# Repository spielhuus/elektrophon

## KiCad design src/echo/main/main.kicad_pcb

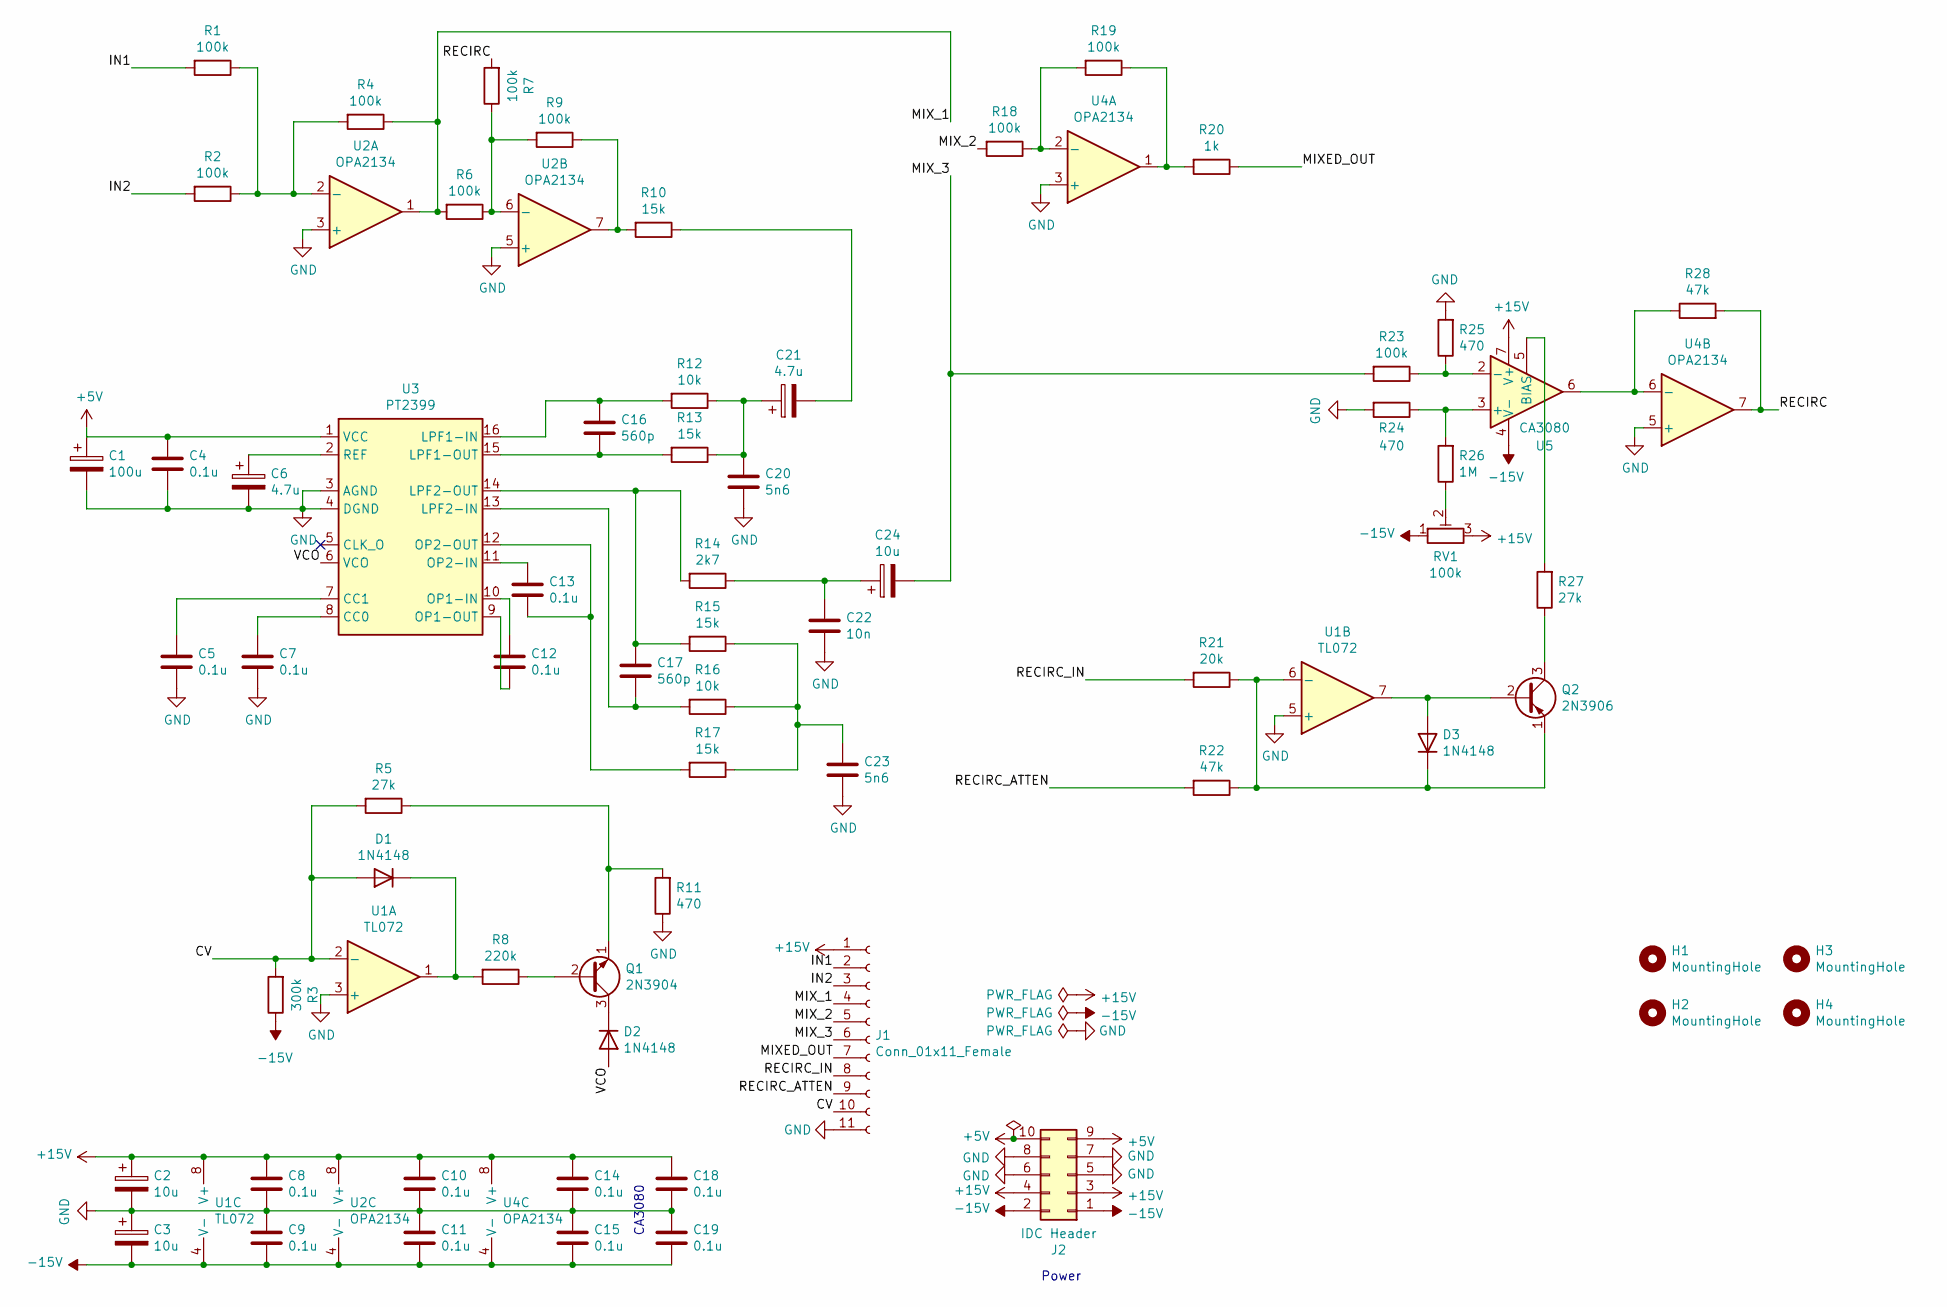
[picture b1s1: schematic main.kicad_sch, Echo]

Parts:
C1: 100u; CP_Radial_D8.0mm_P3.50mm
C2, C3, C24: 10u; CP_Radial_D5.0mm_P2.50mm
C4, C5, C7, C8, C9, C10, C11, C12, C13, C14, C15, C18, C19: 0.1u; C_Rect_L4.0mm_W2.5mm_P2.50mm
C6, C21: 4.7u; CP_Radial_D5.0mm_P2.00mm
C16, C17: 560p; C_Rect_L4.0mm_W2.5mm_P2.50mm
C20, C23: 5n6; C_Rect_L4.6mm_W3.8mm_P2.50mm_MKS02_FKP02
C22: 10n; C_Rect_L4.0mm_W2.5mm_P2.50mm
D1, D2, D3: 1N4148; D_DO-35_SOD27_P7.62mm_Horizontal
H1, H2, H3, H4: MountingHole; MountingHole_2.2mm_M2
J1: Conn_01x11_Female; PinHeader_1x11_P2.54mm_Vertical
J2: IDC Header; IDC-Header_2x05_P2.54mm_Vertical
Q1: 2N3904; TO-92_Inline_Wide
Q2: 2N3906; TO-92_Inline_Wide
R1, R2, R4, R6, R7, R9, R18, R19, R23: 100k; R_Axial_DIN0207_L6.3mm_D2.5mm_P10.16mm_Horizontal
R3: 300k; R_Axial_DIN0207_L6.3mm_D2.5mm_P10.16mm_Horizontal
R5, R27: 27k; R_Axial_DIN0207_L6.3mm_D2.5mm_P10.16mm_Horizontal
R8: 220k; R_Axial_DIN0207_L6.3mm_D2.5mm_P10.16mm_Horizontal
R10, R13, R15, R17: 15k; R_Axial_DIN0207_L6.3mm_D2.5mm_P10.16mm_Horizontal
R11, R24, R25: 470; R_Axial_DIN0207_L6.3mm_D2.5mm_P10.16mm_Horizontal
R12, R16: 10k; R_Axial_DIN0207_L6.3mm_D2.5mm_P10.16mm_Horizontal
R14: 2k7; R_Axial_DIN0207_L6.3mm_D2.5mm_P10.16mm_Horizontal
R20: 1k; R_Axial_DIN0207_L6.3mm_D2.5mm_P10.16mm_Horizontal
R21: 20k; R_Axial_DIN0207_L6.3mm_D2.5mm_P10.16mm_Horizontal
R22, R28: 47k; R_Axial_DIN0207_L6.3mm_D2.5mm_P10.16mm_Horizontal
R26: 1M; R_Axial_DIN0207_L6.3mm_D2.5mm_P10.16mm_Horizontal
RV1: 100k; Potentiometer_Bourns_3296Z_Horizontal
U1: TL072; DIP-8_W7.62mm_Socket
U2, U4: OPA2134; DIP-8_W7.62mm_Socket
U3: PT2399; DIP-16_W7.62mm_Socket
U5: CA3080; DIP-8_W7.62mm_Socket

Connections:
+5V: C1.1, C4.1, J2.9, J2.10, U3.1 (VCC)
+15V: C2.1, C8.1, C10.1, C14.1, C18.1, J1.1, J2.3, J2.4, RV1.3, U1.8 (V+), U2.8 (V+), U4.8 (V+), U5.7 (V+)
-15V: C3.2, C9.2, C11.2, C15.2, C19.2, J2.1, J2.2, R3.1, RV1.1, U1.4 (V-), U2.4 (V-), U4.4 (V-), U5.4 (V-)
/CV: D1.2 (A), J1.10, R3.2, R5.2, U1.2 (-)
/IN1: J1.2, R1.2
/IN2: J1.3, R2.2
/MIXED_OUT: J1.7, R20.1
/MIX_1: J1.4, R4.1, R6.2, U2.1
/MIX_2: J1.5, R18.2
/MIX_3: C24.2, J1.6, R23.2
/RECIRC: R7.2, R28.2, U4.7
/RECIRC_ATTEN: J1.9, R22.2
/RECIRC_IN: J1.8, R21.2
/VCO: D2.2 (A), U3.6 (VCO)
GND: C1.2, C2.2, C3.1, C4.2, C5.2, C6.2, C7.2, C8.2, C9.1, C10.2, C11.1, C14.2, C15.1, C18.2, C19.1, C20.2, C22.2, C23.2, J1.11, J2.5, J2.6, J2.7, J2.8, R11.1, R24.2, R25.2, U1.3 (+), U1.5 (+), U2.3 (+), U2.5 (+), U3.3 (AGND), U3.4 (DGND), U4.3 (+), U4.5 (+)
unnamed: C20.1, C21.1, R12.1, R13.1
unnamed: C21.2, R10.1
unnamed: C22.1, C24.1, R14.1
unnamed: C23.1, R15.1, R16.1, R17.1
unnamed: D1.1 (K), R8.2, U1.1
unnamed: D2.1 (K), Q1.3 (C)
unnamed: D3.2 (A), Q2.2 (B), U1.7
unnamed: D3.1 (K), Q2.1 (E), R21.1, R22.1, U1.6 (-)
unnamed: Q1.2 (B), R8.1
unnamed: Q1.1 (E), R5.1, R11.2
unnamed: Q2.3 (C), R27.1
unnamed: R9.1, R10.2, U2.7
unnamed: R19.1, R20.2, U4.1
unnamed: R26.1, RV1.2
unnamed: R1.1, R2.1, R4.2, U2.2 (-)
unnamed: R6.1, R7.1, R9.2, U2.6 (-)
unnamed: C7.1, U3.8 (CC0)
unnamed: C5.1, U3.7 (CC1)
unnamed: C16.1, R12.2, U3.16 (LPF1-IN)
unnamed: C16.2, R13.2, U3.15 (LPF1-OUT)
unnamed: C17.2, R16.2, U3.13 (LPF2-IN)
unnamed: C17.1, R14.2, R15.2, U3.14 (LPF2-OUT)
unnamed: C12.1, U3.10 (OP1-IN)
unnamed: C12.2, U3.9 (OP1-OUT)
unnamed: C13.1, U3.11 (OP2-IN)
unnamed: C13.2, R17.2, U3.12 (OP2-OUT)
unnamed: C6.1, U3.2 (REF)
unnamed: R18.1, R19.2, U4.2 (-)
unnamed: R28.1, U4.6 (-), U5.6
unnamed: R24.1, R26.2, U5.3 (+)
unnamed: R23.1, R25.1, U5.2 (-)
unnamed: R27.2, U5.5 (BIAS)

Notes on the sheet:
CA3080
Power

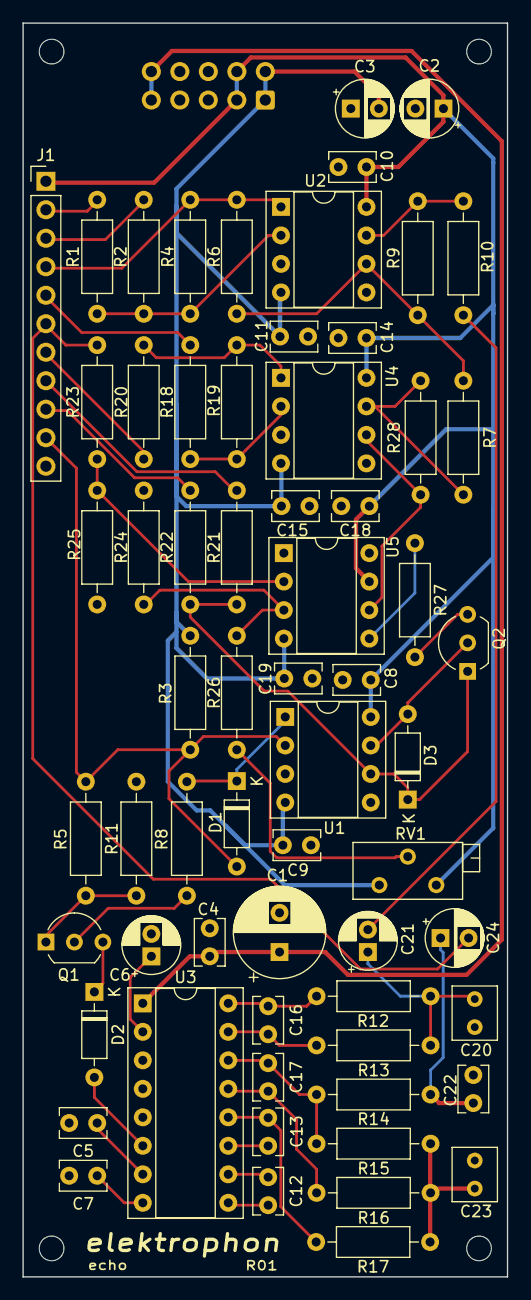
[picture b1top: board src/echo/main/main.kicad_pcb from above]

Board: 2 copper layers, 43.2 x 111.8 mm, 69 parts (1 on the bottom side), 47 nets.

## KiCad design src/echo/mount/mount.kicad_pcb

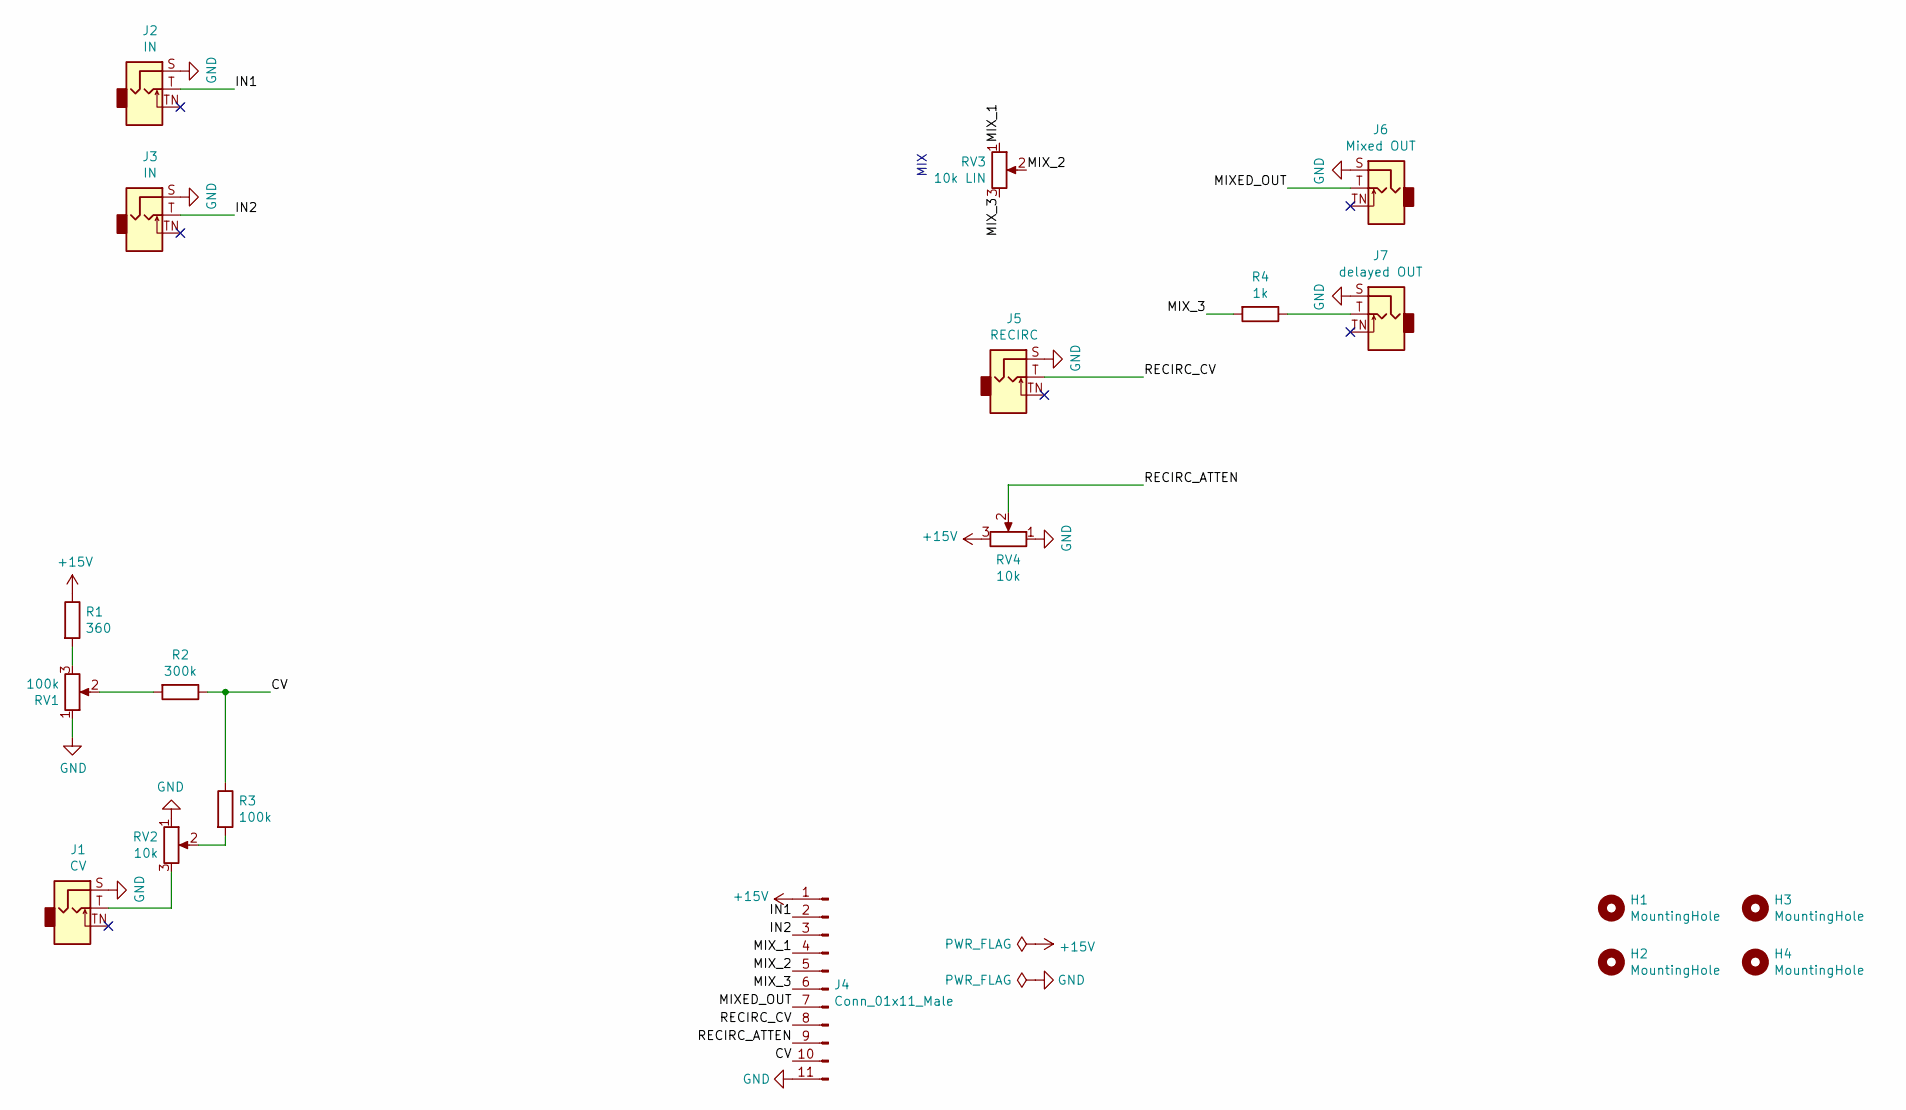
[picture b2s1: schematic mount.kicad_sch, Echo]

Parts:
H1, H2, H3, H4: MountingHole; MountingHole_2.2mm_M2
J1: CV; Jack_3.5mm_WQP-PJ398SM_Vertical
J2, J3: IN; Jack_3.5mm_WQP-PJ398SM_Vertical
J4: Conn_01x11_Male; PinHeader_1x11_P2.54mm_Vertical
J5: RECIRC; Jack_3.5mm_WQP-PJ398SM_Vertical
J6: Mixed OUT; Jack_3.5mm_WQP-PJ398SM_Vertical
J7: delayed OUT; Jack_3.5mm_WQP-PJ398SM_Vertical
R1: 360; R_Axial_DIN0207_L6.3mm_D2.5mm_P10.16mm_Horizontal
R2: 300k; R_Axial_DIN0207_L6.3mm_D2.5mm_P10.16mm_Horizontal
R3: 100k; R_Axial_DIN0207_L6.3mm_D2.5mm_P10.16mm_Horizontal
R4: 1k; R_Axial_DIN0207_L6.3mm_D2.5mm_P10.16mm_Horizontal
RV1: 100k; Potentiometer_Alpha_RD901F-40-00D_Single_Vertical
RV2, RV4: 10k; Potentiometer_Alpha_RD901F-40-00D_Single_Vertical
RV3: 10k LIN; Potentiometer_Alpha_RD901F-40-00D_Single_Vertical

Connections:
+15V: J4.1, R1.1, RV4.3
/CV: J4.10, R2.1, R3.1
/IN1: J2.T, J4.2
/IN2: J3.T, J4.3
/MIXED_OUT: J4.7, J6.T
/MIX_1: J4.4, RV3.1
/MIX_2: J4.5, RV3.2
/MIX_3: J4.6, R4.2, RV3.3
/RECIRC_ATTEN: J4.9, RV4.2
/RECIRC_CV: J4.8, J5.T
GND: J1.S, J2.S, J3.S, J4.11, J5.S, J6.S, J7.S, RV1.1, RV2.1, RV4.1
unnamed: J1.T, RV2.3
unnamed: J7.T, R4.1
unnamed: R1.2, RV1.3
unnamed: R2.2, RV1.2
unnamed: R3.2, RV2.2

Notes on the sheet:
MIX

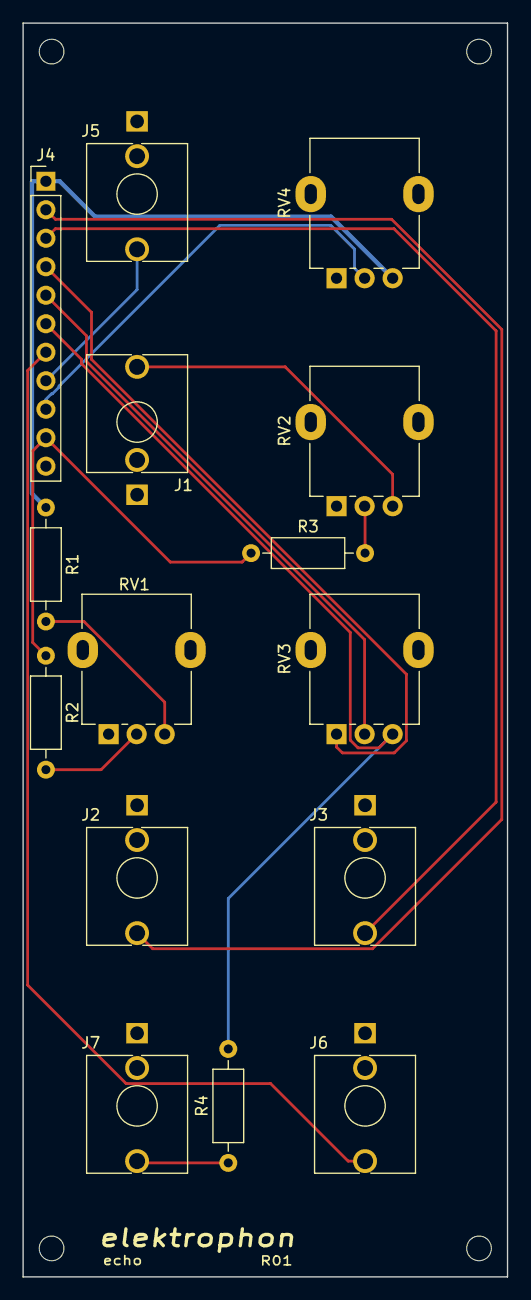
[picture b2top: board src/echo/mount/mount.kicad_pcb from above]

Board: 2 copper layers, 43.2 x 111.8 mm, 19 parts (0 on the bottom side), 16 nets.

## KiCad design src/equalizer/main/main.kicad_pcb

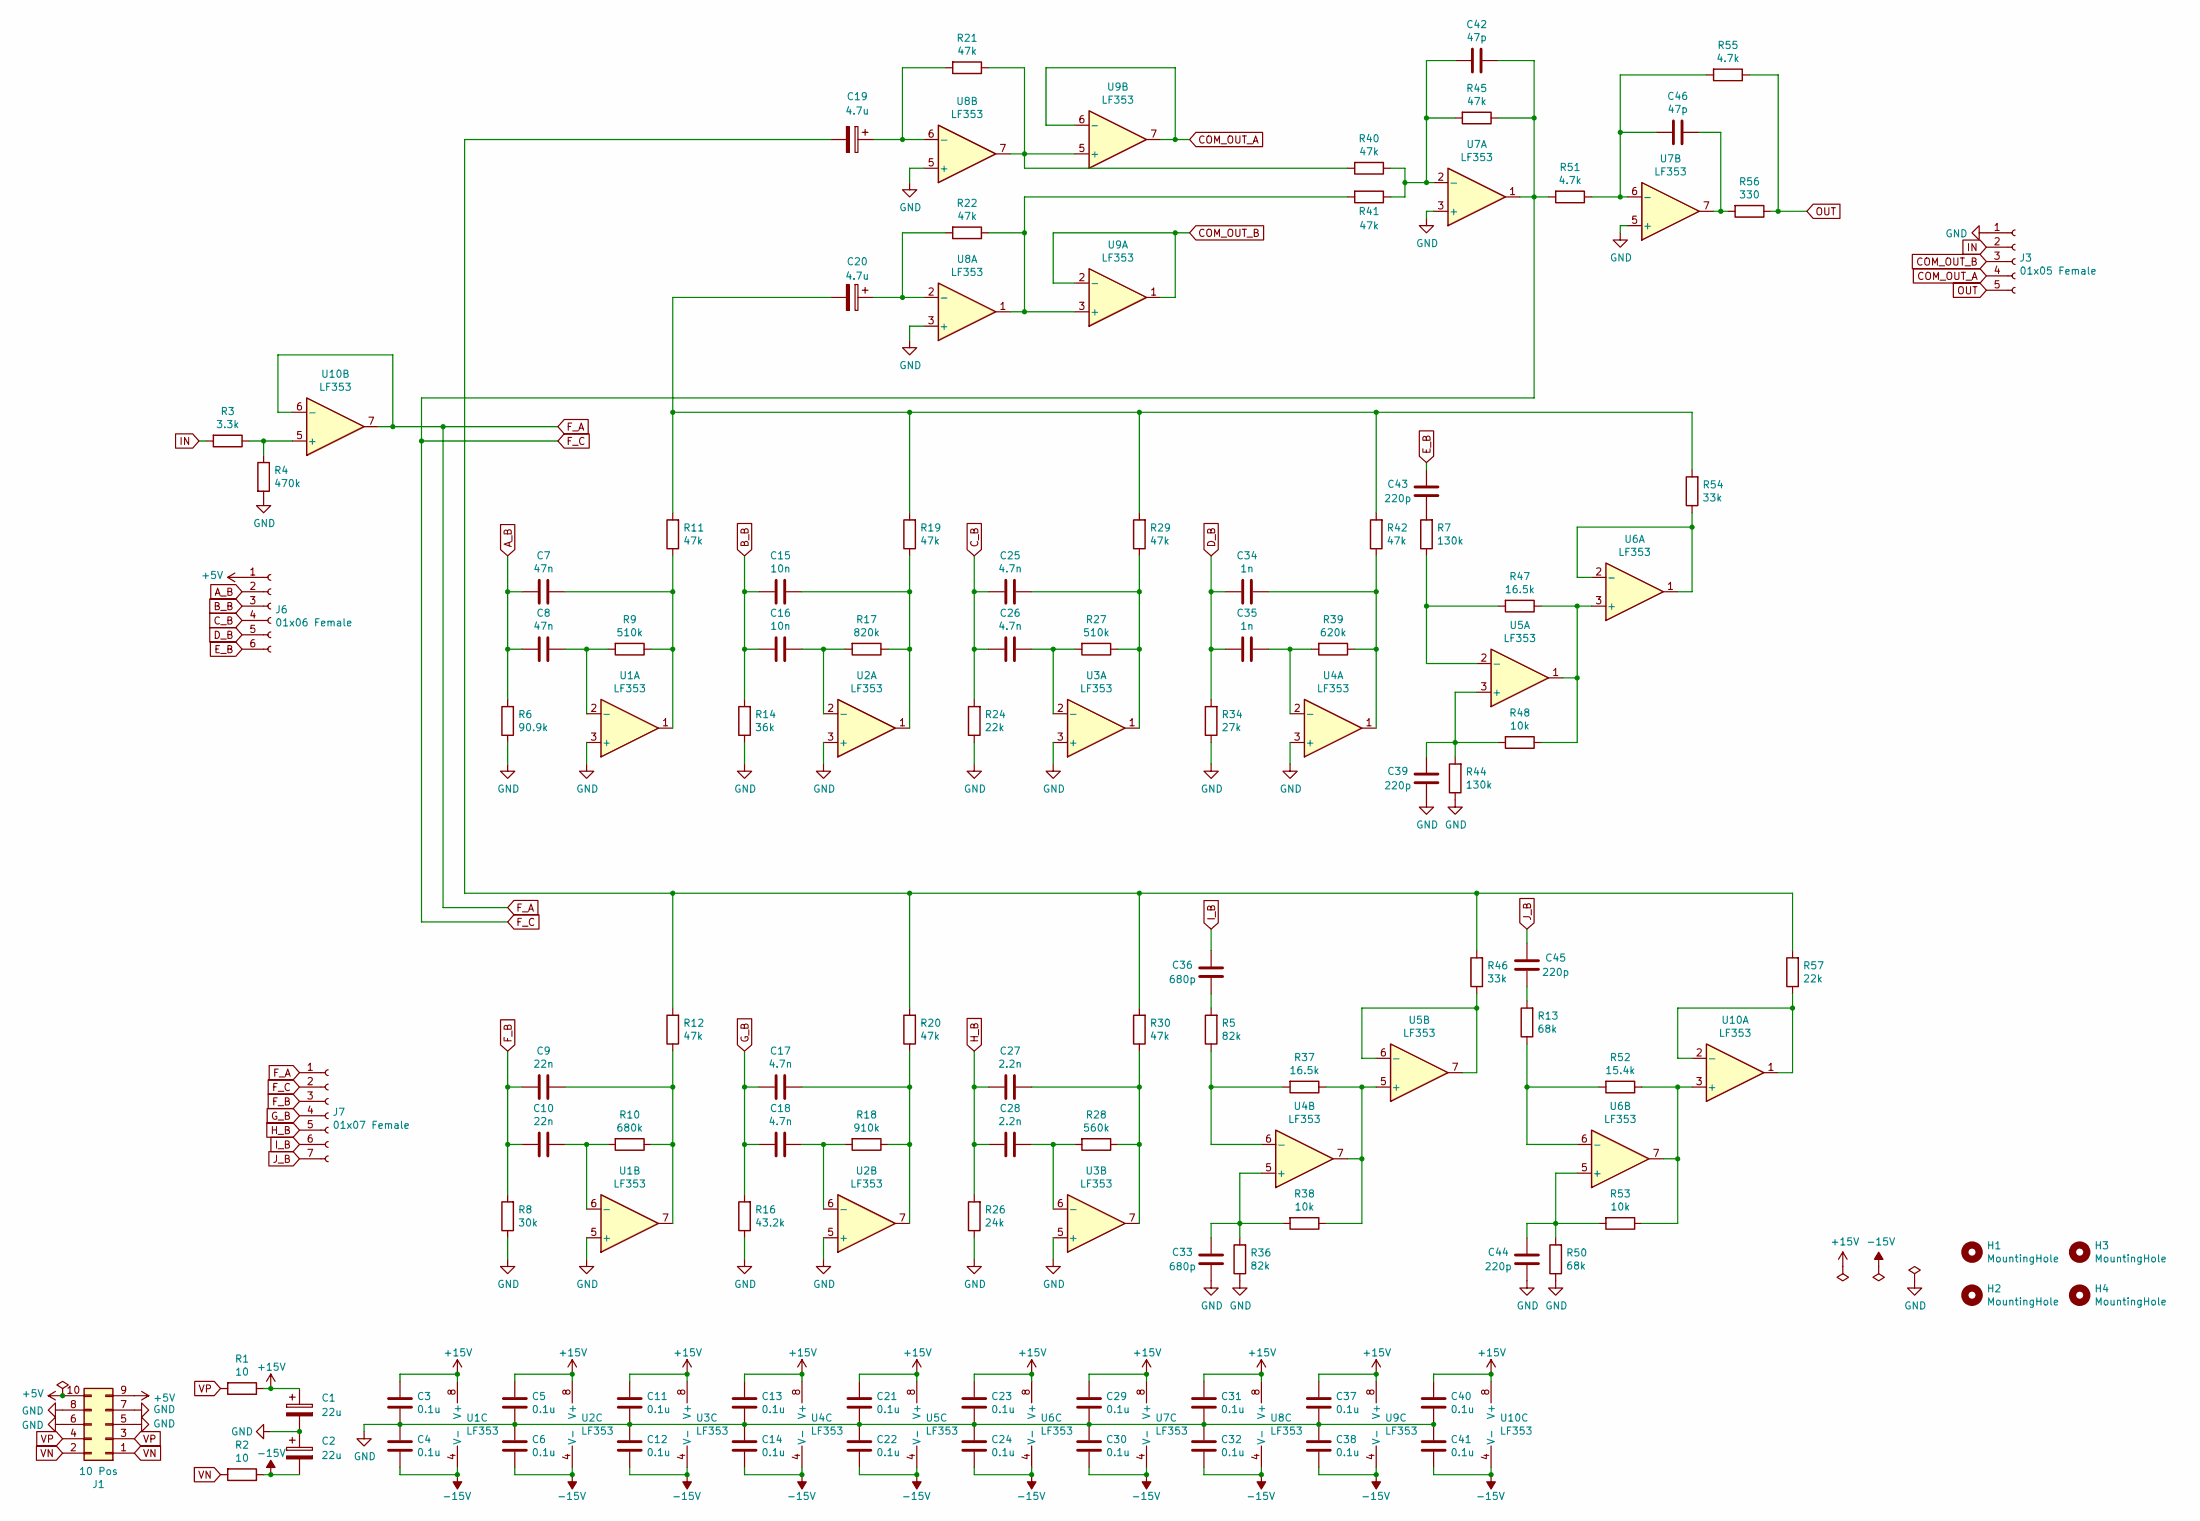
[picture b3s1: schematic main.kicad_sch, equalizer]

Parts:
C1, C2: 22u; CP_Radial_D6.3mm_P2.50mm
C3, C4, C5, C6, C11, C12, C13, C14, C21, C22, C23, C24, C29, C30, C31, C32, C37, C38, C40, C41: 0.1u; C_Disc_D3.8mm_W2.6mm_P2.50mm
C7, C8: 47n; C_Rect_L7.2mm_W3.5mm_P5.00mm_FKS2_FKP2_MKS2_MKP2
C9, C10: 22n; C_Rect_L7.2mm_W3.0mm_P5.00mm_FKS2_FKP2_MKS2_MKP2
C15, C16: 10n; C_Rect_L7.2mm_W3.0mm_P5.00mm_FKS2_FKP2_MKS2_MKP2
C17, C18, C25, C26: 4.7n; C_Rect_L7.2mm_W4.5mm_P5.00mm_FKS2_FKP2_MKS2_MKP2
C19, C20: 4.7u; CP_Radial_D5.0mm_P2.50mm
C27, C28: 2.2n; C_Rect_L7.2mm_W4.5mm_P5.00mm_FKS2_FKP2_MKS2_MKP2
C33, C36: 680p; C_Rect_L7.0mm_W4.5mm_P5.00mm
C34, C35: 1n; C_Rect_L7.2mm_W4.5mm_P5.00mm_FKS2_FKP2_MKS2_MKP2
C39, C43, C44, C45: 220p; C_Rect_L7.2mm_W4.5mm_P5.00mm_FKS2_FKP2_MKS2_MKP2
C42, C46: 47p; C_Disc_D3.8mm_W2.6mm_P2.50mm
H1, H2, H3, H4: MountingHole; MountingHole_2.2mm_M2
J1: 10 Pos; IDC-Header_2x05_P2.54mm_Vertical
J3: 01x05 Female; PinSocket_1x05_P2.54mm_Vertical
J6: 01x06 Female; PinSocket_1x06_P2.54mm_Vertical
J7: 01x07 Female; PinSocket_1x07_P2.54mm_Vertical
R1, R2: 10; R_Axial_DIN0204_L3.6mm_D1.6mm_P5.08mm_Horizontal
R3: 3.3k; R_Axial_DIN0204_L3.6mm_D1.6mm_P5.08mm_Horizontal
R4: 470k; R_Axial_DIN0204_L3.6mm_D1.6mm_P5.08mm_Horizontal
R5, R36: 82k; R_Axial_DIN0204_L3.6mm_D1.6mm_P5.08mm_Horizontal
R6: 90.9k; R_Axial_DIN0204_L3.6mm_D1.6mm_P5.08mm_Horizontal
R7, R44: 130k; R_Axial_DIN0204_L3.6mm_D1.6mm_P5.08mm_Horizontal
R8: 30k; R_Axial_DIN0204_L3.6mm_D1.6mm_P5.08mm_Horizontal
R9, R27: 510k; R_Axial_DIN0204_L3.6mm_D1.6mm_P2.54mm_Vertical
R10: 680k; R_Axial_DIN0204_L3.6mm_D1.6mm_P2.54mm_Vertical
R11, R12, R19, R20, R21, R22, R29, R30, R40, R41, R42, R45: 47k; R_Axial_DIN0204_L3.6mm_D1.6mm_P5.08mm_Horizontal
R13, R50: 68k; R_Axial_DIN0204_L3.6mm_D1.6mm_P5.08mm_Horizontal
R14: 36k; R_Axial_DIN0204_L3.6mm_D1.6mm_P5.08mm_Horizontal
R16: 43.2k; R_Axial_DIN0204_L3.6mm_D1.6mm_P5.08mm_Horizontal
R17: 820k; R_Axial_DIN0204_L3.6mm_D1.6mm_P2.54mm_Vertical
R18: 910k; R_Axial_DIN0204_L3.6mm_D1.6mm_P2.54mm_Vertical
R24, R57: 22k; R_Axial_DIN0204_L3.6mm_D1.6mm_P5.08mm_Horizontal
R26: 24k; R_Axial_DIN0204_L3.6mm_D1.6mm_P5.08mm_Horizontal
R28: 560k; R_Axial_DIN0204_L3.6mm_D1.6mm_P2.54mm_Vertical
R34: 27k; R_Axial_DIN0204_L3.6mm_D1.6mm_P5.08mm_Horizontal
R37, R47: 16.5k; R_Axial_DIN0204_L3.6mm_D1.6mm_P5.08mm_Horizontal
R38, R48, R53: 10k; R_Axial_DIN0204_L3.6mm_D1.6mm_P5.08mm_Horizontal
R39: 620k; R_Axial_DIN0207_L6.3mm_D2.5mm_P2.54mm_Vertical
R46, R54: 33k; R_Axial_DIN0204_L3.6mm_D1.6mm_P5.08mm_Horizontal
R51, R55: 4.7k; R_Axial_DIN0204_L3.6mm_D1.6mm_P5.08mm_Horizontal
R52: 15.4k; R_Axial_DIN0204_L3.6mm_D1.6mm_P5.08mm_Horizontal
R56: 330; R_Axial_DIN0204_L3.6mm_D1.6mm_P5.08mm_Horizontal
U1, U2, U3, U4, U5, U6, U7, U8, U9, U10: LF353; DIP-8_W7.62mm_Socket

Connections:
+5V: J1.9, J1.10, J6.1
+15V: C1.1, C3.2, C5.2, C11.2, C13.2, C21.2, C23.2, C29.2, C31.2, C37.2, C40.2, R1.1, U1.8 (V+), U2.8 (V+), U3.8 (V+), U4.8 (V+), U5.8 (V+), U6.8 (V+), U7.8 (V+), U8.8 (V+), U9.8 (V+), U10.8 (V+)
-15V: C2.2, C4.1, C6.1, C12.1, C14.1, C22.1, C24.1, C30.1, C32.1, C38.1, C41.1, R2.1, U1.4 (V-), U2.4 (V-), U3.4 (V-), U4.4 (V-), U5.4 (V-), U6.4 (V-), U7.4 (V-), U8.4 (V-), U9.4 (V-), U10.4 (V-)
A_B: C7.2, C8.2, J6.2, R6.2
B_B: C15.2, C16.2, J6.3, R14.2
COM_OUT_A: J3.4, U9.6 (-), U9.7
COM_OUT_B: J3.3, U9.1, U9.2 (-)
C_B: C25.2, C26.2, J6.4, R24.2
D_B: C34.2, C35.2, J6.5, R34.2
E_B: C43.2, J6.6
F_A: J7.1, U10.6 (-), U10.7
F_B: C9.2, C10.2, J7.3, R8.2
F_C: C42.1, J7.2, R45.1, R51.2, U7.1
GND: C1.2, C2.1, C3.1, C4.2, C5.1, C6.2, C11.1, C12.2, C13.1, C14.2, C21.1, C22.2, C23.1, C24.2, C29.1, C30.2, C31.1, C32.2, C33.1, C37.1, C38.2, C39.1, C40.1, C41.2, C44.1, J1.5, J1.6, J1.7, J1.8, J3.1, R4.2, R6.1, R8.1, R14.1, R16.1, R24.1, R26.1, R34.1, R36.1, R44.1, R50.1, U1.3 (+), U1.5 (+), U2.3 (+), U2.5 (+), U3.3 (+), U3.5 (+), U4.3 (+), U7.3 (+), U7.5 (+), U8.3 (+), U8.5 (+)
G_B: C17.2, C18.2, J7.4, R16.2
H_B: C27.2, C28.2, J7.5, R26.2
IN: J3.2, R3.2
I_B: C36.2, J7.6
J_B: C45.2, J7.7
unnamed: C7.1, R9.1, R11.1, U1.1
unnamed: C9.1, R10.1, R12.1, U1.7
unnamed: C15.1, R17.1, R19.1, U2.1
unnamed: C17.1, R18.1, R20.1, U2.7
unnamed: C19.2, R12.2, R20.2, R30.2, R46.2, R57.2
unnamed: C20.2, R11.2, R19.2, R29.2, R42.2, R54.2
unnamed: C25.1, R27.1, R29.1, U3.1
unnamed: C27.1, R28.1, R30.1, U3.7
unnamed: C34.1, R39.1, R42.1, U4.1
unnamed: C36.1, R5.2
unnamed: C43.1, R7.2
unnamed: C45.1, R13.2
unnamed: C46.1, R56.2, U7.7
unnamed: C8.1, R9.2, U1.2 (-)
unnamed: C10.1, R10.2, U1.6 (-)
unnamed: C16.1, R17.2, U2.2 (-)
unnamed: C18.1, R18.2, U2.6 (-)
unnamed: C26.1, R27.2, U3.2 (-)
unnamed: C28.1, R28.2, U3.6 (-)
unnamed: C35.1, R39.2, U4.2 (-)
unnamed: C33.2, R36.2, R38.2, U4.5 (+)
unnamed: R5.1, R37.2, U4.6 (-)
unnamed: C39.2, R44.2, R48.2, U5.3 (+)
unnamed: R7.1, R47.2, U5.2 (-)
unnamed: R37.1, R38.1, U4.7, U5.5 (+)
unnamed: R46.1, U5.6 (-), U5.7
unnamed: R47.1, R48.1, U5.1, U6.3 (+)
unnamed: R54.1, U6.1, U6.2 (-)
unnamed: C44.2, R50.2, R53.2, U6.5 (+)
unnamed: R13.1, R52.2, U6.6 (-)
unnamed: C42.2, R40.1, R41.1, R45.2, U7.2 (-)
unnamed: C46.2, R51.1, R55.2, U7.6 (-)
unnamed: C20.1, R22.2, U8.2 (-)
unnamed: C19.1, R21.2, U8.6 (-)
unnamed: R22.1, R41.2, U8.1, U9.3 (+)
unnamed: R21.1, R40.2, U8.7, U9.5 (+)
unnamed: R52.1, R53.1, U6.7, U10.3 (+)
unnamed: R57.1, U10.1, U10.2 (-)
unnamed: R3.1, R4.1, U10.5 (+)
OUT: J3.5, R55.1, R56.1
VN: J1.1, J1.2, R2.2
VP: J1.3, J1.4, R1.2

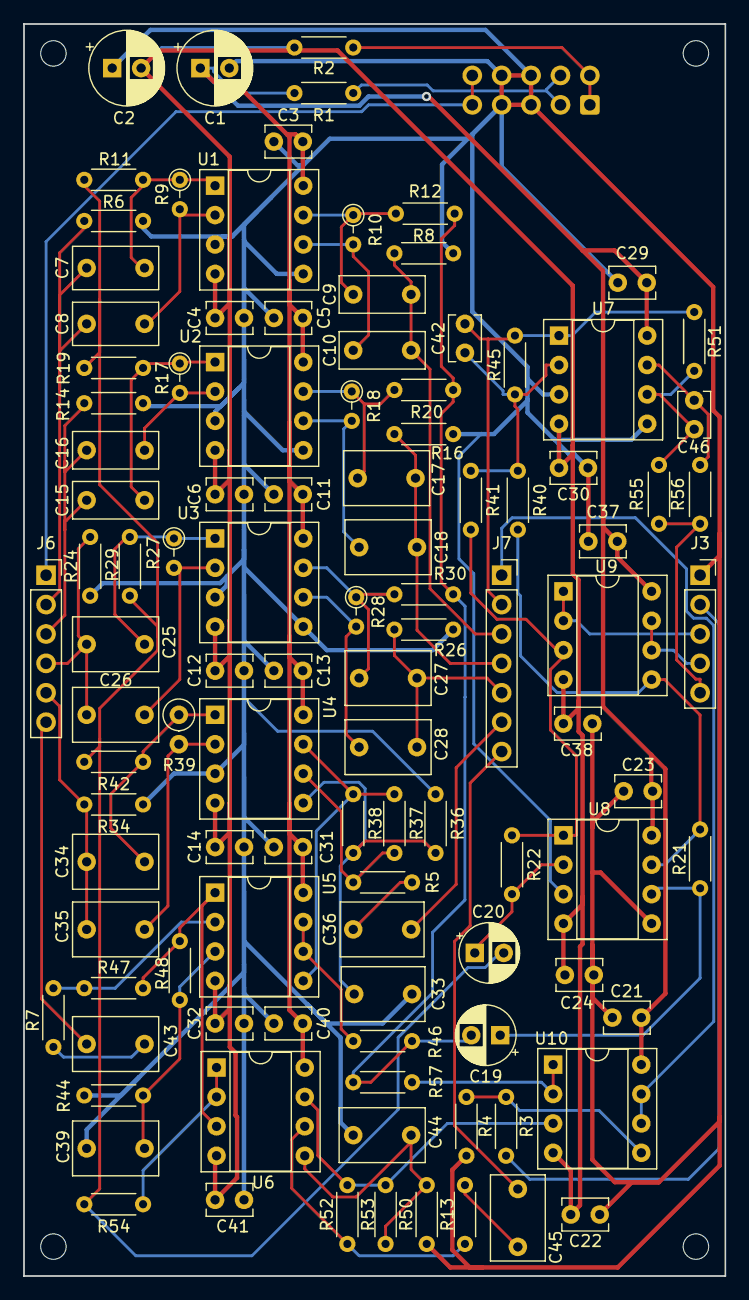
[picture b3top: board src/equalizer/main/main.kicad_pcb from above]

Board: 2 copper layers, 60.6 x 108.2 mm, 112 parts (1 on the bottom side), 61 nets.

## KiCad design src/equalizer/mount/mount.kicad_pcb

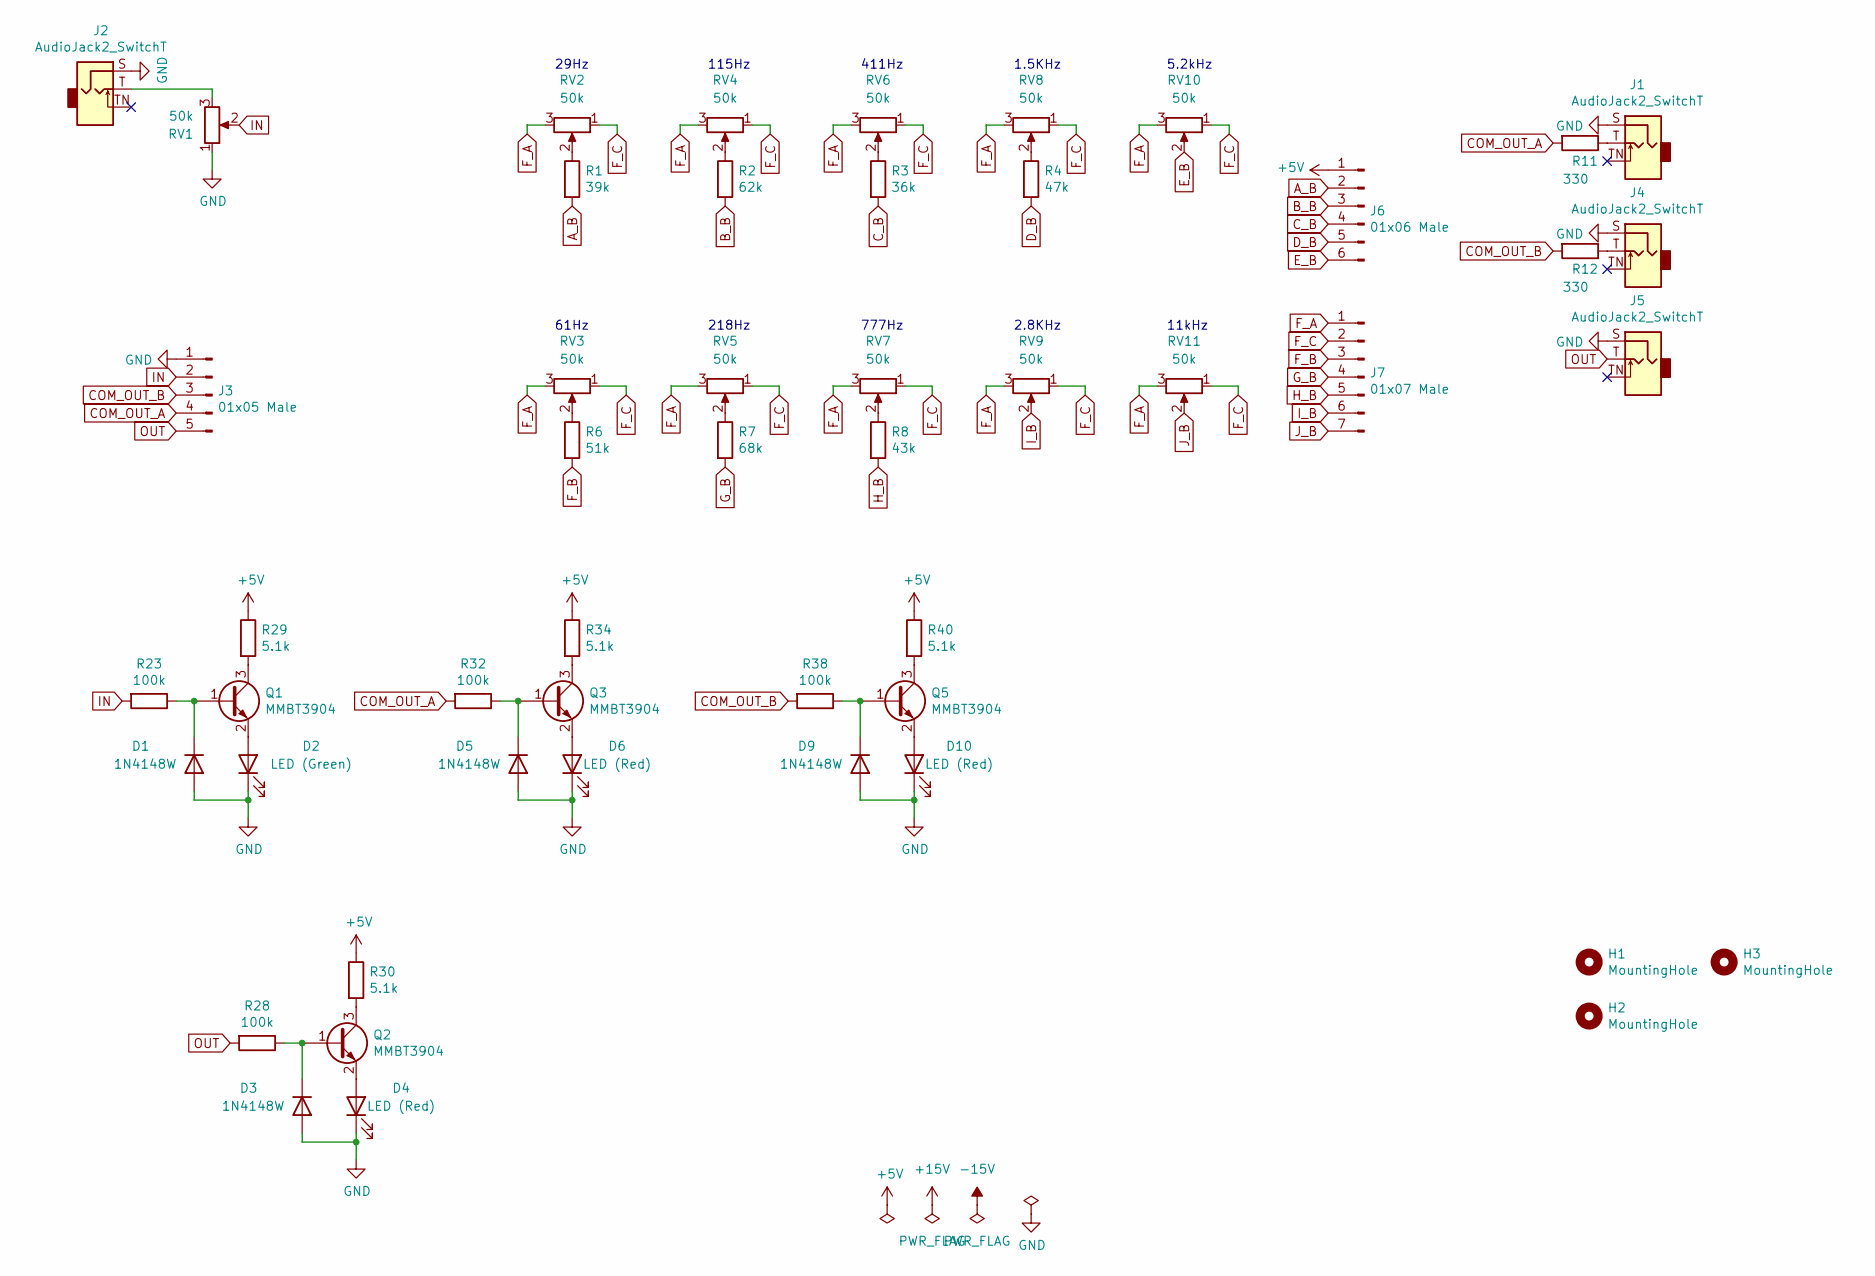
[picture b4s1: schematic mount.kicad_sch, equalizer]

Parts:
D1, D3, D5, D9: 1N4148W; D_SOD-123
D2: LED (Green); LED_D3.0mm
D4, D6, D10: LED (Red); LED_D3.0mm
H1, H2, H3: MountingHole; MountingHole_2.2mm_M2
J1, J2, J4, J5: AudioJack2_SwitchT; Jack_3.5mm_WQP-PJ398SM_Vertical
J3: 01x05 Male; PinHeader_1x05_P2.54mm_Vertical
J6: 01x06 Male; PinHeader_1x06_P2.54mm_Vertical
J7: 01x07 Male; PinHeader_1x07_P2.54mm_Vertical
Q1, Q2, Q3, Q5: MMBT3904; SOT-23
R1: 39k; R_Axial_DIN0204_L3.6mm_D1.6mm_P5.08mm_Horizontal
R2: 62k; R_Axial_DIN0204_L3.6mm_D1.6mm_P5.08mm_Horizontal
R3: 36k; R_Axial_DIN0204_L3.6mm_D1.6mm_P5.08mm_Horizontal
R4: 47k; R_Axial_DIN0204_L3.6mm_D1.6mm_P5.08mm_Horizontal
R6: 51k; R_Axial_DIN0204_L3.6mm_D1.6mm_P5.08mm_Horizontal
R7: 68k; R_Axial_DIN0204_L3.6mm_D1.6mm_P5.08mm_Horizontal
R8: 43k; R_Axial_DIN0204_L3.6mm_D1.6mm_P5.08mm_Horizontal
R11, R12: 330; R_Axial_DIN0204_L3.6mm_D1.6mm_P5.08mm_Horizontal
R23, R28, R32, R38: 100k; R_0805_2012Metric_Pad1.20x1.40mm_HandSolder
R29, R30, R34, R40: 5.1k; R_0805_2012Metric_Pad1.20x1.40mm_HandSolder
RV1, RV2, RV3, RV4, RV5, RV6, RV7, RV8, RV9, RV10, RV11: 50k; Potentiometer_Alpha_RD901F-40-00D_Single_Vertical

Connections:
+5V: J6.1, R29.1, R30.1, R34.1, R40.1
A_B: J6.2, R1.2
B_B: J6.3, R2.2
COM_OUT_A: J3.4, R11.2, R32.2
COM_OUT_B: J3.3, R12.2, R38.2
C_B: J6.4, R3.2
D_B: J6.5, R4.2
E_B: J6.6, RV10.2
F_A: J7.1, RV2.3, RV3.3, RV4.3, RV5.3, RV6.3, RV7.3, RV8.3, RV9.3, RV10.3, RV11.3
F_B: J7.3, R6.2
F_C: J7.2, RV2.1, RV3.1, RV4.1, RV5.1, RV6.1, RV7.1, RV8.1, RV9.1, RV10.1, RV11.1
GND: D1.2 (A), D2.1 (K), D3.2 (A), D4.1 (K), D5.2 (A), D6.1 (K), D9.2 (A), D10.1 (K), J1.S, J2.S, J3.1, J4.S, J5.S, RV1.1
G_B: J7.4, R7.2
H_B: J7.5, R8.2
IN: J3.2, R23.2, RV1.2
I_B: J7.6, RV9.2
J_B: J7.7, RV11.2
unnamed: D1.1 (K), Q1.1 (B), R23.1
unnamed: D2.2 (A), Q1.2 (E)
unnamed: D3.1 (K), Q2.1 (B), R28.1
unnamed: D4.2 (A), Q2.2 (E)
unnamed: D5.1 (K), Q3.1 (B), R32.1
unnamed: D6.2 (A), Q3.2 (E)
unnamed: D9.1 (K), Q5.1 (B), R38.1
unnamed: D10.2 (A), Q5.2 (E)
unnamed: J1.T, R11.1
unnamed: J2.T, RV1.3
unnamed: J4.T, R12.1
unnamed: Q1.3 (C), R29.2
unnamed: Q2.3 (C), R30.2
unnamed: Q3.3 (C), R34.2
unnamed: Q5.3 (C), R40.2
unnamed: R1.1, RV2.2
unnamed: R2.1, RV4.2
unnamed: R3.1, RV6.2
unnamed: R4.1, RV8.2
unnamed: R6.1, RV3.2
unnamed: R7.1, RV5.2
unnamed: R8.1, RV7.2
OUT: J3.5, J5.T, R28.2

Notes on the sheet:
11kHz
1.5KHz
777Hz
61Hz
218Hz
29Hz
2.8KHz
115Hz
5.2kHz
411Hz

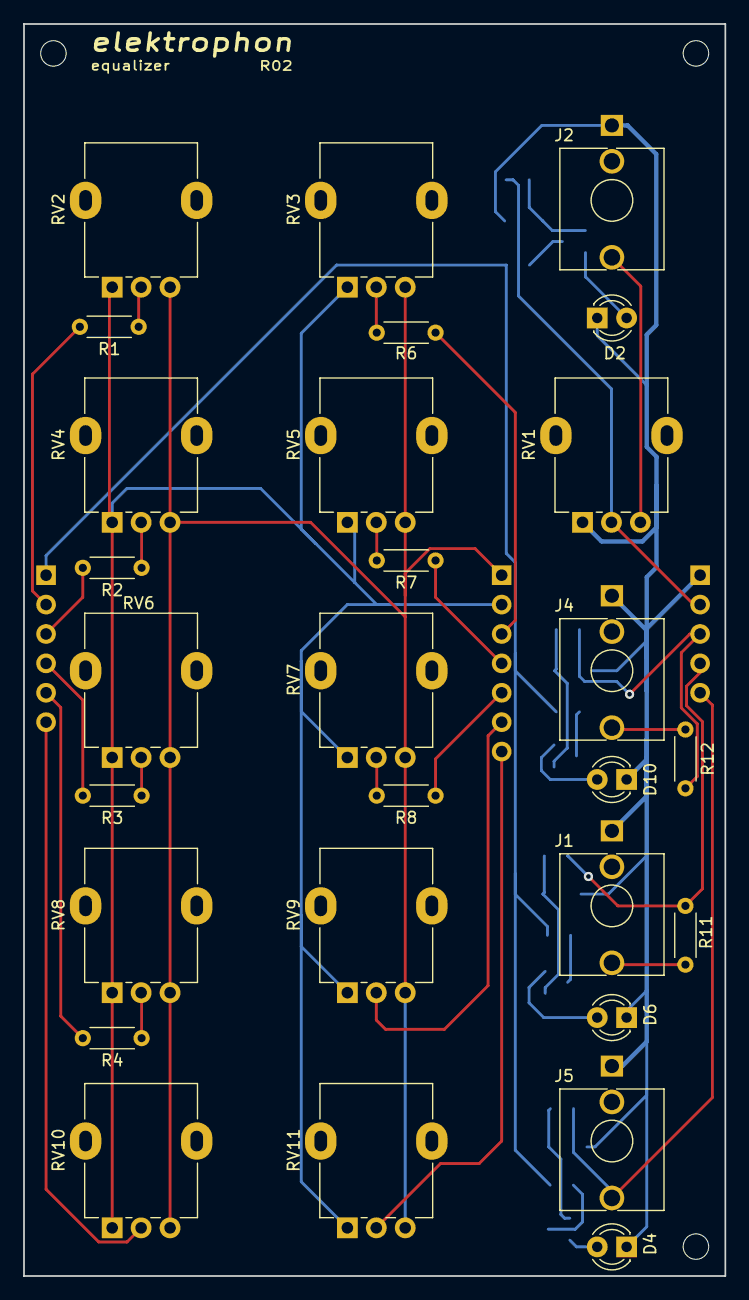
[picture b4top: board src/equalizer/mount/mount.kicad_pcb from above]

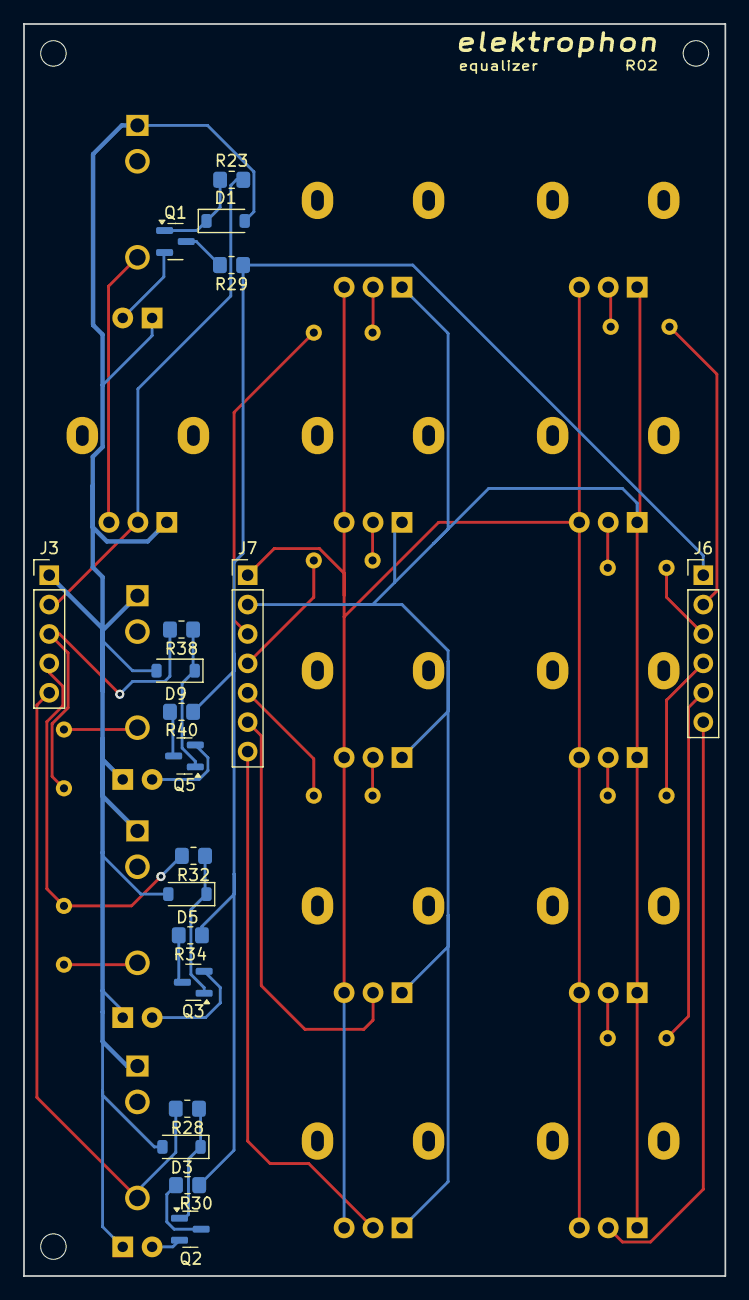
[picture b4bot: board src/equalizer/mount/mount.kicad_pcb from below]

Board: 2 copper layers, 60.6 x 108.2 mm, 50 parts (19 on the bottom side), 40 nets.

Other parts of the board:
H4: MountingHole; MountingHole_2.2mm_M2

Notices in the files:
src/basspp/main/main.kicad_sch:
License CC BY 4.0 - Attribution 4.0 International
